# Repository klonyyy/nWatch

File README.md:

# nWatch
My wristwatch code repository

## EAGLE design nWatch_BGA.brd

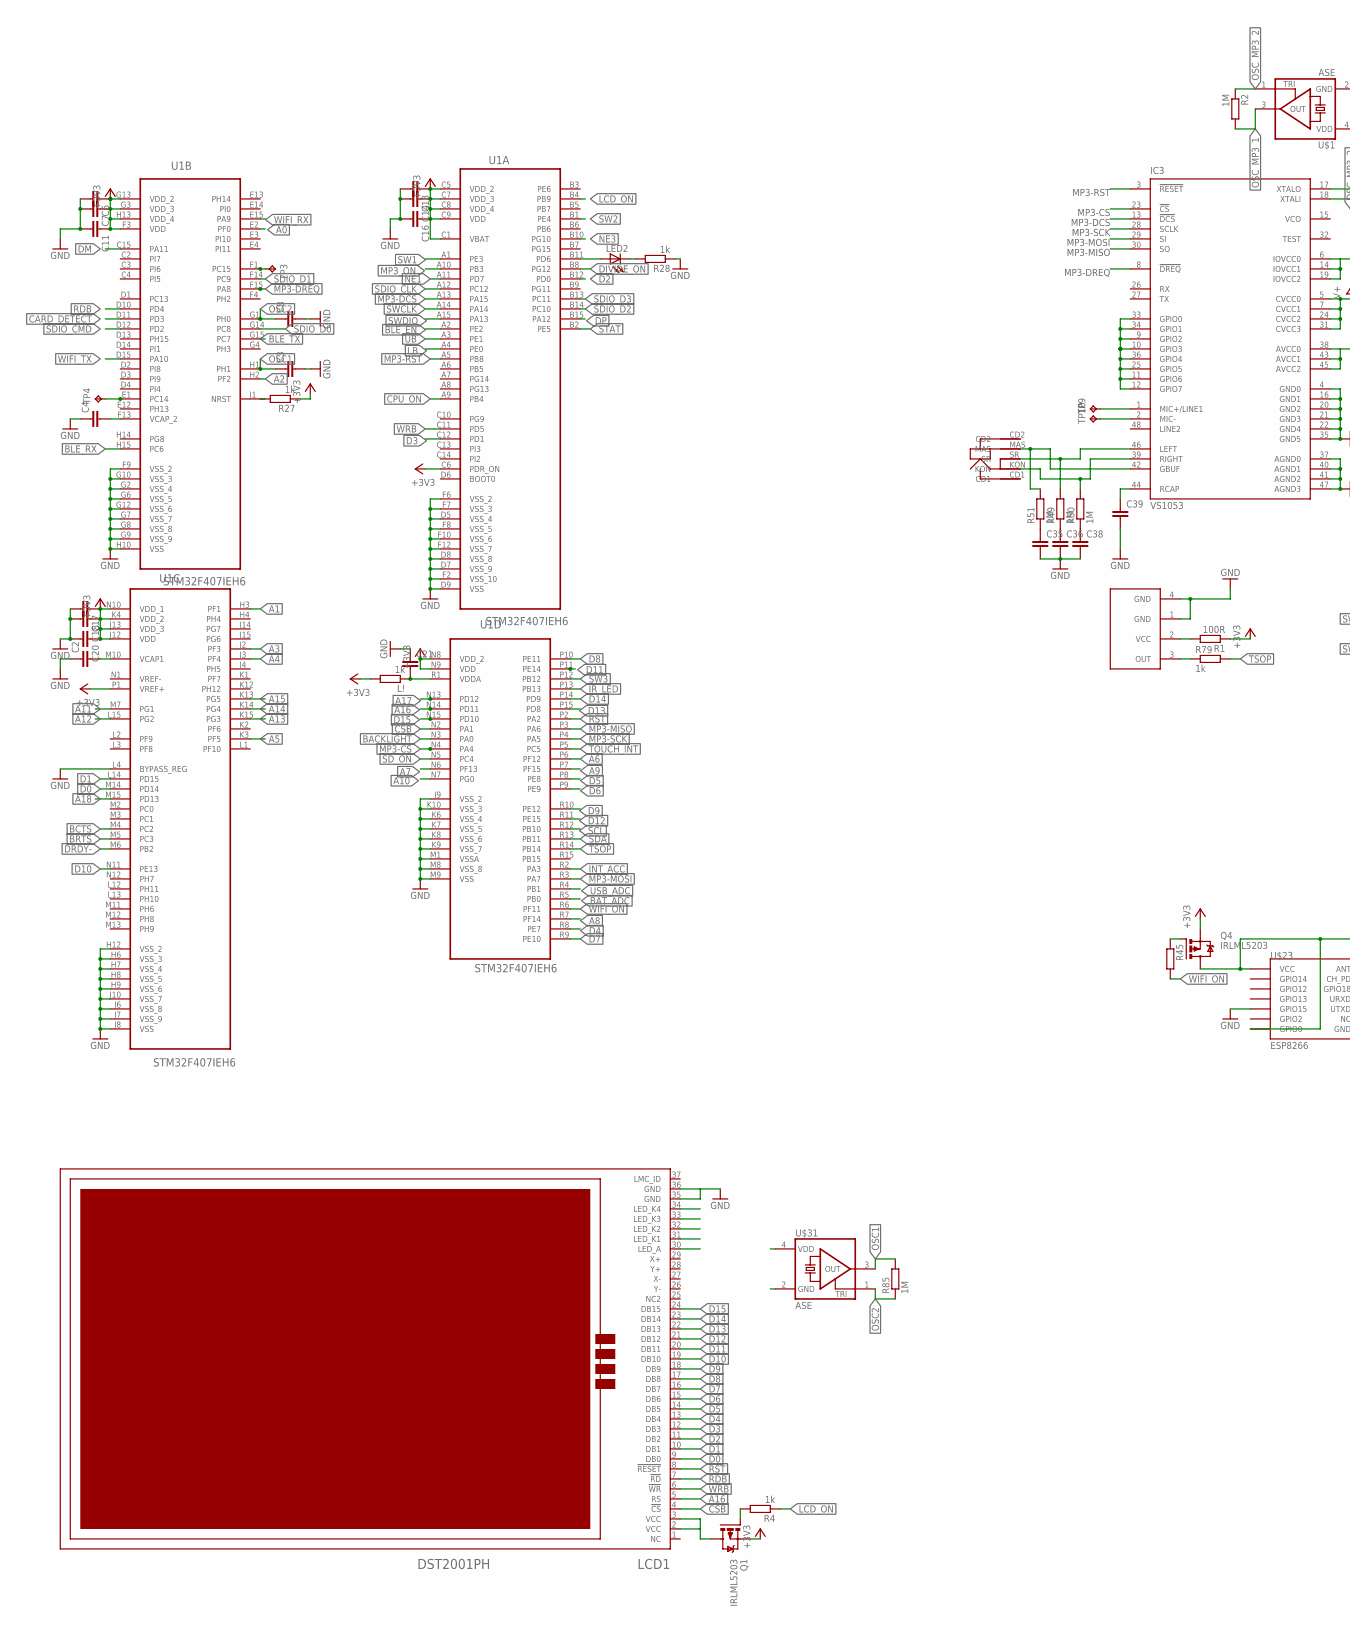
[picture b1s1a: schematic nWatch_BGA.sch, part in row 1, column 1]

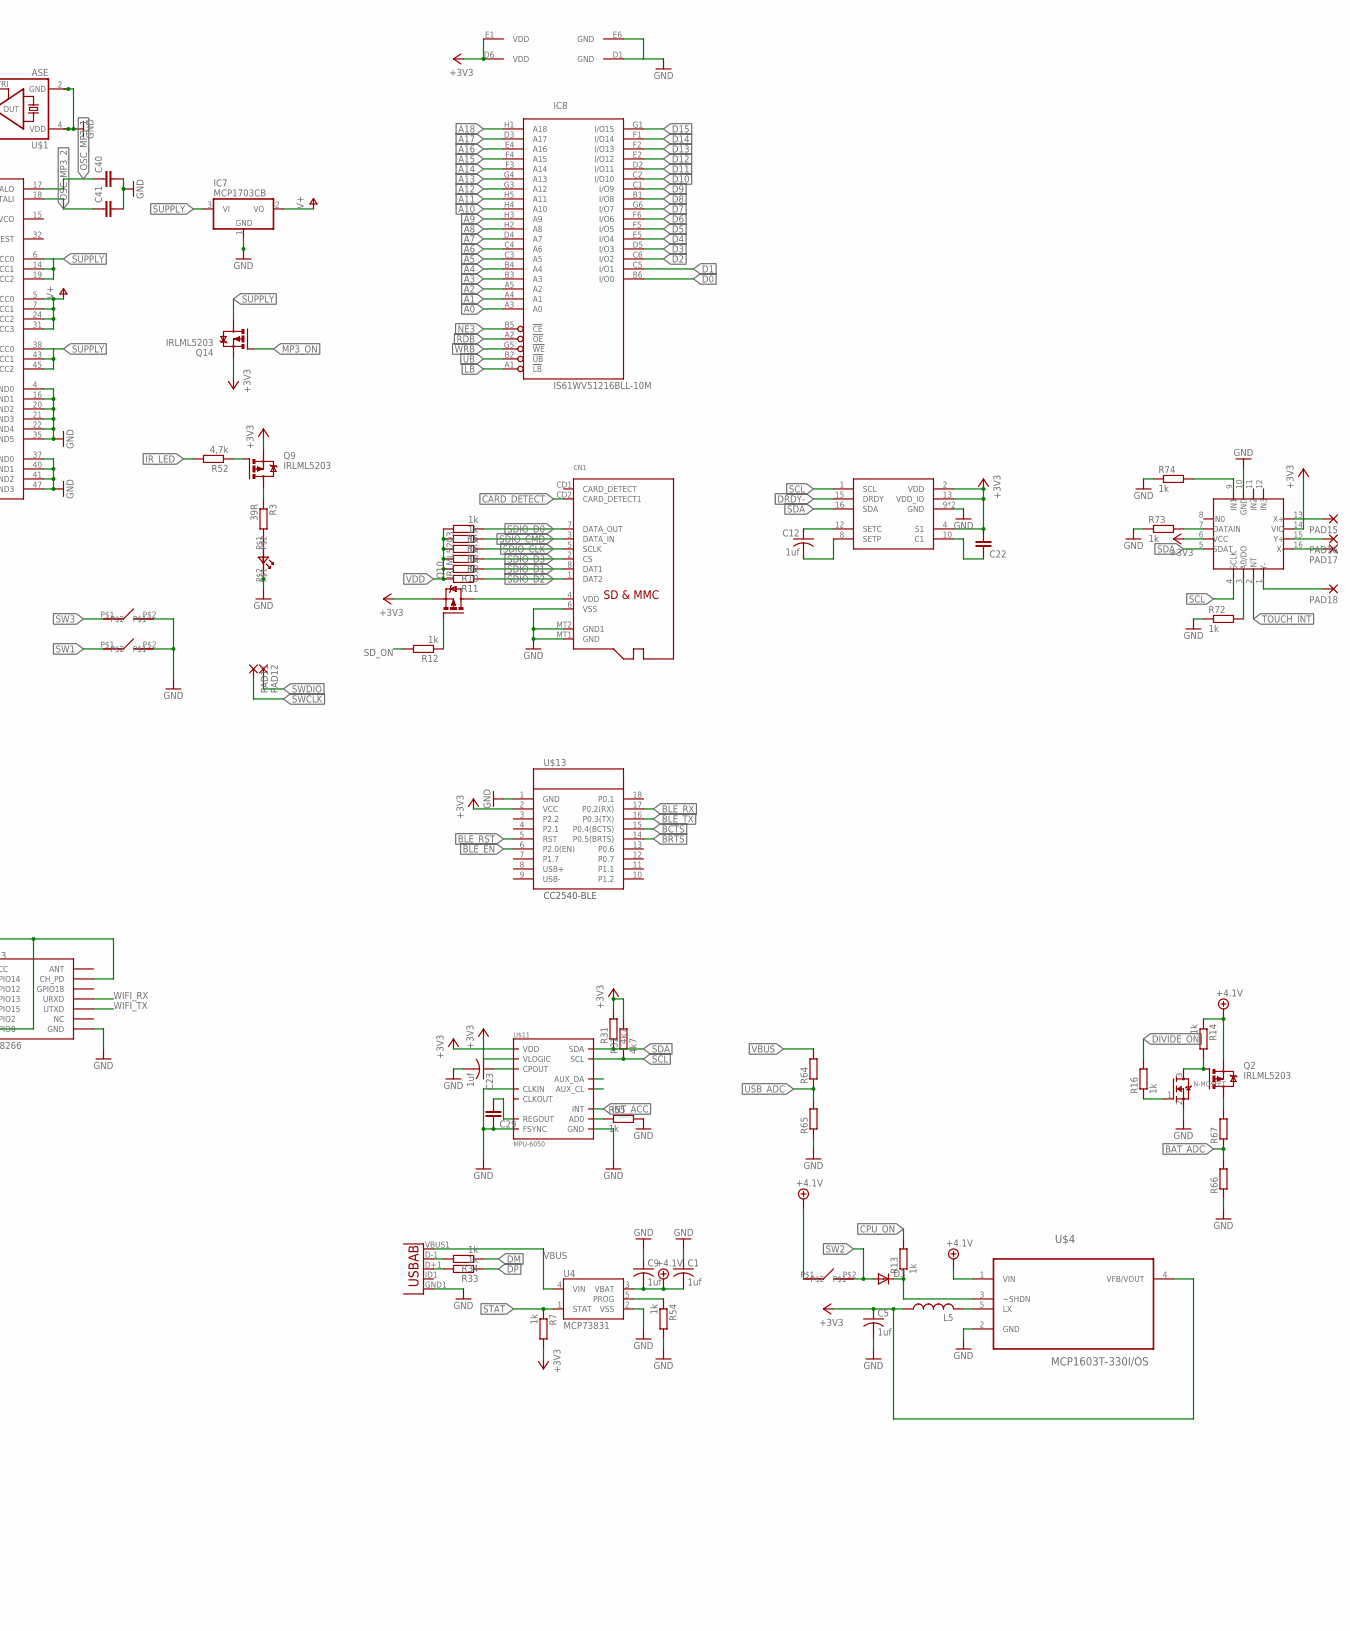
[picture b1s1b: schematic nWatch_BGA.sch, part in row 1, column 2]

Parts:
C1, C5, C9, C12, C23: 1uf; C0805K
C2, C3, C4, C6, C7, C8, C11, C13, C14, C16, C17, C18, C20, C21, C35, C36, C38, C39, C40, C41: C-EUC0402; C0402
C22, C29: C-EUC0603K; C0603K
CN1: MICROSD
D3: MBR0520LT; SOD123
IC3: VS1053; LQFP-48
IC7: MCP1703CB; SOT23
IC8: IS61WV51216BLL-10M; TFBGA48_9X11
L5: L-USL2825P; L2825P
L!: 1k; R0402
LCD1: DST2001PH
LED2: LEDCHIPLED_0603; CHIPLED_0603
N-MOSFET: MOSFET-NREFLOW; SOT23
PAD11, PAD12, PAD15, PAD16, PAD17, PAD18: SMD2; SMD1,27-2,54
Q1, Q2, Q4, Q9, Q10, Q14: IRLML5203; MICRO3
R1: 100R; R0402
R2, R49, R50, R51, R85: 1M; R0402
R3: 39R; R0402
R4, R5, R6, R7, R8, R9, R10, R11, R12, R13, R14, R16, R27, R28, R33, R34, R54, R55, R72, R73, R74, R79: 1k; R0402
R31, R32: 4k7; R0402
R45: R-EU_R0603; R0603
R52: 4,7k; R0402
R64, R65, R66, R67: R-EU_R0402; R0402
TP3, TP4, TP9, TP10: TPTP08SQ; TP08SQ
U1: STM32F407IEH6; BGA176C65P15X15_1000X1000X60
U4: MCP73831; SOT23-5
U5: USB""; USB-MICRO-SMD
U$1, U$31: ASE
U$2: TSOP77338TS; TSOP77338
U$4: MCP1603T-330I/OS; SOT95P280X110-5N
U$5, U$16, U$30: SWITCHSMD
U$11: MPU-6050; QFN.24.4X4
U$12: HMC5883L; LPCC16
U$13: MOJ_BLEMOJ_BLE; CC2540-MINI-BLE
U$15: STMPE811; QFN-16
U$23: ESP8266; ESP-03
U$26: VISHAY_IRLED
U$32: MOJ_JACK

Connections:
+3V3: C5.1, C6.1, C7.1, C11.1, C13.1, C14.1, C16.1, C17.1, C18.1, C20.1, C22.2, IC8.D6 (VDD), IC8.E1 (VDD), L5.1, L!.2, Q1.2 (S), Q4.2 (S), Q9.2 (S), Q10.2 (S), Q14.2 (S), R1.1, R7.2, R27.1, R31.2, R32.2, U1.C1 (VBAT), U1.C5 (VDD_2), U1.C6 (PDR_ON), U1.C7 (VDD_3), U1.C8 (VDD_4), U1.C9 (VDD), U1.F3 (VDD), U1.G3 (VDD_3), U1.G13 (VDD_2), U1.H13 (VDD_4), U1.J12 (VDD), U1.J13 (VDD_3), U1.K4 (VDD_2), U1.N8 (VDD_2), U1.N9 (VDD), U1.N10 (VDD_1), U1.P1 (VREF+), U$4.4 (VFB/VOUT), U$11.8 (VLOGIC), U$11.13 (VDD), U$12.2 (VDD), U$12.4 (S1), U$12.13 (VDD_IO), U$13.2 (VCC), U$15.6 (VCC), U$15.14 (VIO)
+4.1V: C1.2, C9.2, Q2.2 (S), R14.1, U4.3 (VBAT), U$4.1 (VIN), U$5.P$1
A0: IC8.A3 (A0), U1.E2 (PF0)
A1: IC8.A4 (A1), U1.H3 (PF1)
A2: IC8.A5 (A2), U1.H2 (PF2)
A3: IC8.B3 (A3), U1.J2 (PF3)
A4: IC8.B4 (A4), U1.J3 (PF4)
A5: IC8.C3 (A5), U1.K3 (PF5)
A6: IC8.C4 (A6), U1.P6 (PF12)
A7: IC8.D4 (A7), U1.N6 (PF13)
A8: IC8.H2 (A8), U1.R7 (PF14)
A9: IC8.H3 (A9), U1.P7 (PF15)
A10: IC8.H4 (A10), U1.N7 (PG0)
A11: IC8.H5 (A11), U1.M7 (PG1)
A12: IC8.G3 (A12), U1.L15 (PG2)
A13: IC8.G4 (A13), U1.K15 (PG3)
A14: IC8.F3 (A14), U1.K14 (PG4)
A15: IC8.F4 (A15), U1.K13 (PG5)
A16: IC8.E4 (A16), LCD1.5 (RS), U1.N14 (PD11)
A17: IC8.D3 (A17), U1.N13 (PD12)
A18: IC8.H1 (A18), U1.M15 (PD13)
BACKLIGHT: U1.N3 (PA0)
BAT_ADC: R66.2, R67.1, U1.R5 (PB0)
BCTS: U1.M4 (PC2), U$13.15 (P0.4(BCTS))
BLE_EN: U1.A2 (PE2), U$13.6 (P2.0(EN))
BLE_RST: U$13.5 (RST)
BLE_RX: U1.H15 (PC6), U$13.17 (P0.2(RX))
BLE_TX: U1.G15 (PC7), U$13.16 (P0.3(TX))
BRTS: U1.M5 (PC3), U$13.14 (P0.5(BRTS))
CARD_DETECT: CN1.CD2 (CARD_DETECT1), U1.D11 (PD3)
CPU_ON: R13.2, U1.A9 (PB4)
CSB: LCD1.4 (!CS), U1.N2 (PA1)
D0: IC8.B6 (I/O0), LCD1.9 (DB0), U1.M14 (PD14)
D1: IC8.C5 (I/O1), LCD1.10 (DB1), U1.L14 (PD15)
D2: IC8.C6 (I/O2), LCD1.11 (DB2), U1.B12 (PD0)
D3: IC8.D5 (I/O3), LCD1.12 (DB3), U1.C12 (PD1)
D4: IC8.E5 (I/O4), LCD1.13 (DB4), U1.R8 (PE7)
D5: IC8.F5 (I/O5), LCD1.14 (DB5), U1.P8 (PE8)
D6: IC8.F6 (I/O6), LCD1.15 (DB6), U1.P9 (PE9)
D7: IC8.G6 (I/O7), LCD1.16 (DB7), U1.R9 (PE10)
D8: IC8.B1 (I/O8), LCD1.17 (DB8), U1.P10 (PE11)
D9: IC8.C1 (I/O9), LCD1.18 (DB9), U1.R10 (PE12)
D10: IC8.C2 (I/O10), LCD1.19 (DB10), U1.N11 (PE13)
D11: IC8.D2 (I/O11), LCD1.20 (DB11), U1.P11 (PE14)
D12: IC8.E2 (I/O12), LCD1.21 (DB12), U1.R11 (PE15)
D13: IC8.F2 (I/O13), LCD1.22 (DB13), U1.P15 (PD8)
D14: IC8.F1 (I/O14), LCD1.23 (DB14), U1.P14 (PD9)
D15: IC8.G1 (I/O15), LCD1.24 (DB15), U1.N15 (PD10)
DIVIDE_ON: R16.2, U1.B8 (PG12)
DM: R34.1, U1.C15 (PA11)
DP: R33.1, U1.B15 (PA12)
DRDY-: U1.M6 (PB2), U$12.15 (DRDY)
GND: C1.1, C2.1, C3.2, C4.1, C5.2, C6.2, C7.2, C8.2, C9.1, C11.2, C13.2, C14.2, C16.2, C17.2, C18.2, C20.2, C21.1, C23.2, C29.1, C35.2, C36.2, C38.2, C39.2, C40.2, C41.2, CN1.6 (VSS), CN1.MT1 (GND), CN1.MT2 (GND1), IC3.4 (GND0), IC3.16 (GND1), IC3.20 (GND2), IC3.21 (GND3), IC3.22 (GND4), IC3.35 (GND5), IC3.37 (AGND0), IC3.40 (AGND1), IC3.41 (AGND2), IC3.47 (AGND3), IC7.1 (GND), IC8.D1 (GND), IC8.E6 (GND), LCD1.35 (GND), LCD1.36 (GND), N-MOSFET.2 (S), R28.1, R54.2, R55.2, R65.1, R66.1, R72.1, R73.1, R74.1, U1.D5 (VSS_4), U1.D7 (VSS_9), U1.D8 (VSS_8), U1.D9 (VSS), U1.F2 (VSS_10), U1.F6 (VSS_2), U1.F7 (VSS_3), U1.F8 (VSS_5), U1.F9 (VSS_2), U1.F10 (VSS_6), U1.F12 (VSS_7), U1.G2 (VSS_4), U1.G6 (VSS_5), U1.G7 (VSS_7), U1.G8 (VSS_8), U1.G9 (VSS_9), U1.G10 (VSS_3), U1.G12 (VSS_6), U1.H6 (VSS_3), U1.H7 (VSS_4), U1.H8 (VSS_5), U1.H9 (VSS_6), U1.H10 (VSS), U1.H12 (VSS_2), U1.J6 (VSS_8), U1.J7 (VSS_9), U1.J8 (VSS), U1.J9 (VSS_2), U1.J10 (VSS_7), U1.K6 (VSS_4), U1.K7 (VSS_5), U1.K8 (VSS_6), U1.K9 (VSS_7), U1.K10 (VSS_3), U1.L4 (BYPASS_REG), U1.M1 (VSSA), U1.M8 (VSS_8), U1.M9 (VSS), U4.2 (VSS), U5.GND1 (GND), U$1.2 (GND), U$1.4 (VDD), U$2.1 (GND), U$2.4 (GND), U$4.2 (GND), U$11.1 (CLKIN), U$11.11 (FSYNC), U$11.18 (GND), U$12.9 (GND), U$12.11 (GND), U$13.1 (GND), U$15.10 (GND), U$16.P$2, U$23.GND, U$23.GPIO15, U$26.P$2, U$30.P$2, U$31.2 (GND), U$31.4 (VDD)
INT_ACC: U1.R2 (PA3), U$11.12 (INT)
IR_LED: R52.2, U1.P13 (PB13)
LB: IC8.A1 (!LB), U1.A4 (PE0)
LCD_ON: R4.1, U1.B4 (PB9)
MP3-CS: IC3.23 (!CS), U1.N4 (PA4)
MP3-DCS: IC3.13 (!DCS), U1.A13 (PA15)
MP3-DREQ: IC3.8 (!DREQ), U1.F15 (PA8)
MP3-MISO: IC3.30 (SO), U1.P3 (PA6)
MP3-MOSI: IC3.29 (SI), U1.R3 (PA7)
MP3-RST: IC3.3 (!RESET), U1.A5 (PB8)
MP3-SCK: IC3.28 (SCLK), U1.P4 (PA5)
MP3_ON: Q14.1 (G), U1.A10 (PB3)
unnamed: LCD1.2 (VCC), LCD1.3 (VCC), Q1.3 (D)
unnamed: Q1.1 (G), R4.2
unnamed: R79.1, U$2.3 (OUT)
unnamed: R3.2, U$26.P$1
unnamed: C21.2, L!.1, U1.R1 (VDDA)
unnamed: N-MOSFET.3 (D), Q2.1 (G), R14.2
unnamed: C2.2, U1.M10 (VCAP1)
unnamed: C4.2, U1.F13 (VCAP_2)
unnamed: D3.C, R13.1, U$4.3 (~SHDN)
unnamed: N-MOSFET.1 (G), R16.1
unnamed: L5.2, U$4.5 (LX)
unnamed: Q2.3 (D), R67.2
unnamed: TP4.TP, U1.E1 (PC14)
unnamed: TP3.TP, U1.F1 (PC15)
unnamed: R27.2, U1.J1 (NRST)
unnamed: LED2.A, U1.B11 (PD6)
unnamed: LED2.C, R28.2
unnamed: C23.1, U$11.20 (CPOUT)
unnamed: R55.1, U$11.9 (AD0)
unnamed: R54.1, U4.5 (PROG)
unnamed: R33.2, U5.D+1 (D+)
unnamed: R34.2, U5.D-1 (D-)
unnamed: C12.1, U$12.12 (SETC)
unnamed: C12.2, U$12.8 (SETP)
unnamed: C22.1, U$12.10 (C1)
unnamed: C29.2, U$11.10 (REGOUT)
unnamed: R73.2, U$15.7 (DATAIN)
unnamed: R74.2, U$15.9 (IN1)
unnamed: R72.2, U$15.3 (A0/DO)
unnamed: Q10.1 (G), R12.1
unnamed: IC3.42 (GBUF), R51.2, U$32.MAS
unnamed: IC3.46 (LEFT), R49.2, U$32.SR
unnamed: IC3.39 (RIGHT), R50.2, U$32.KON
unnamed: C39.1, IC3.44 (RCAP)
unnamed: IC3.9 (GPIO2), IC3.10 (GPIO3), IC3.11 (GPIO6), IC3.12 (GPIO7), IC3.25 (GPIO5), IC3.33 (GPIO0), IC3.34 (GPIO1), IC3.36 (GPIO4)
unnamed: Q9.1 (G), R52.1
unnamed: Q9.3 (D), R3.1
unnamed: Q4.3 (D), U$23.CH_PD, U$23.GPIO0, U$23.VCC
unnamed: Q4.1 (G), R45.1
unnamed: C35.1, R51.1
unnamed: C36.1, R49.1
unnamed: C38.1, R50.1
unnamed: PAD18.1, U$15.1 (Y-)
unnamed: PAD17.1, U$15.16 (X-)
unnamed: PAD15.1, U$15.13 (X+)
unnamed: PAD16.1, U$15.15 (Y+)
unnamed: R1.2, U$2.2 (VCC)
unnamed: IC3.2 (MIC-), TP10.TP
unnamed: IC3.1 (MIC+/LINE1), TP9.TP
NE1: U1.A11 (PD7)
NE3: IC8.B5 (!CE), U1.B10 (PG10)
OSC1: C3.1, R85.2, U1.H1, U$31.3 (OUT)
OSC2: C8.1, R85.1, U1.G1 (PH0), U$31.1 (TRI)
OSC_MP3_1: C40.1, IC3.17 (XTALO), R2.2, U$1.3 (OUT)
OSC_MP3_2: C41.1, IC3.18 (XTALI), R2.1, U$1.1 (TRI)
P2.2: U$13.3 (P2.2)
RDB: IC8.A2 (!OE), LCD1.7 (!RD), U1.D10 (PD4)
RST: LCD1.8 (!RESET), U1.P2 (PA2)
SCL: R32.1, U1.R12 (PB10), U$11.23 (SCL), U$12.1 (SCL), U$15.4 (SCLK)
SDA: R31.1, U1.R13 (PB11), U$11.24 (SDA), U$12.16 (SDA), U$15.5 (SDAT)
SDIO_CLK: CN1.5 (SCLK), R8.1, U1.A12 (PC12)
SDIO_CMD: CN1.3 (DATA_IN), R6.1, U1.D12 (PD2)
SDIO_D0: CN1.7 (DATA_OUT), R5.1, U1.G14 (PC8)
SDIO_D1: CN1.8 (DAT1), R10.1, U1.F14 (PC9)
SDIO_D2: CN1.1 (DAT2), R11.1, U1.B14 (PC10)
SDIO_D3: CN1.2 (CS), R9.1, U1.B13 (PC11)
SD_ON: R12.2, U1.N5 (PC4)
STAT: R7.1, U1.B2 (PE5), U4.1 (STAT)
SUPPLY: IC3.6 (IOVCC0), IC3.14 (IOVCC1), IC3.19 (IOVCC2), IC3.38 (AVCC0), IC3.43 (AVCC1), IC3.45 (AVCC2), IC7.3 (VI), Q14.3 (D)
SW1: U1.A1 (PE3), U$16.P$1
SW2: D3.A, U1.B1 (PE4), U$5.P$2
SW3: U1.P12 (PB12), U$30.P$1
SWCLK: PAD11.1, U1.A14
SWDIO: PAD12.1, U1.A15 (PA13)
TOUCH_INT: U1.P5 (PC5), U$15.2 (INT)
TSOP: R79.2, U1.R14 (PB14)
UB: IC8.B2 (!UB), U1.A3 (PE1)
USB_ADC: R64.1, R65.2, U1.R4 (PB1)
V+: IC3.5 (CVCC0), IC3.7 (CVCC1), IC3.24 (CVCC2), IC3.31 (CVCC3), IC7.2 (VO)
VBUS: R64.2, U4.4 (VIN), U5.VBUS1 (VBUS)
VDD: CN1.4 (VDD), Q10.3 (D), R5.2, R6.2, R8.2, R9.2, R10.2, R11.2
VREF-: U1.N1 (VREF-)
WIFI_ON: R45.2, U1.R6 (PF11)
WIFI_RX: U1.E15 (PA9), U$23.URXD
WIFI_TX: U1.D15 (PA10), U$23.UTXD
WRB: IC8.G5 (!WE), LCD1.6 (!WR), U1.C11 (PD5)

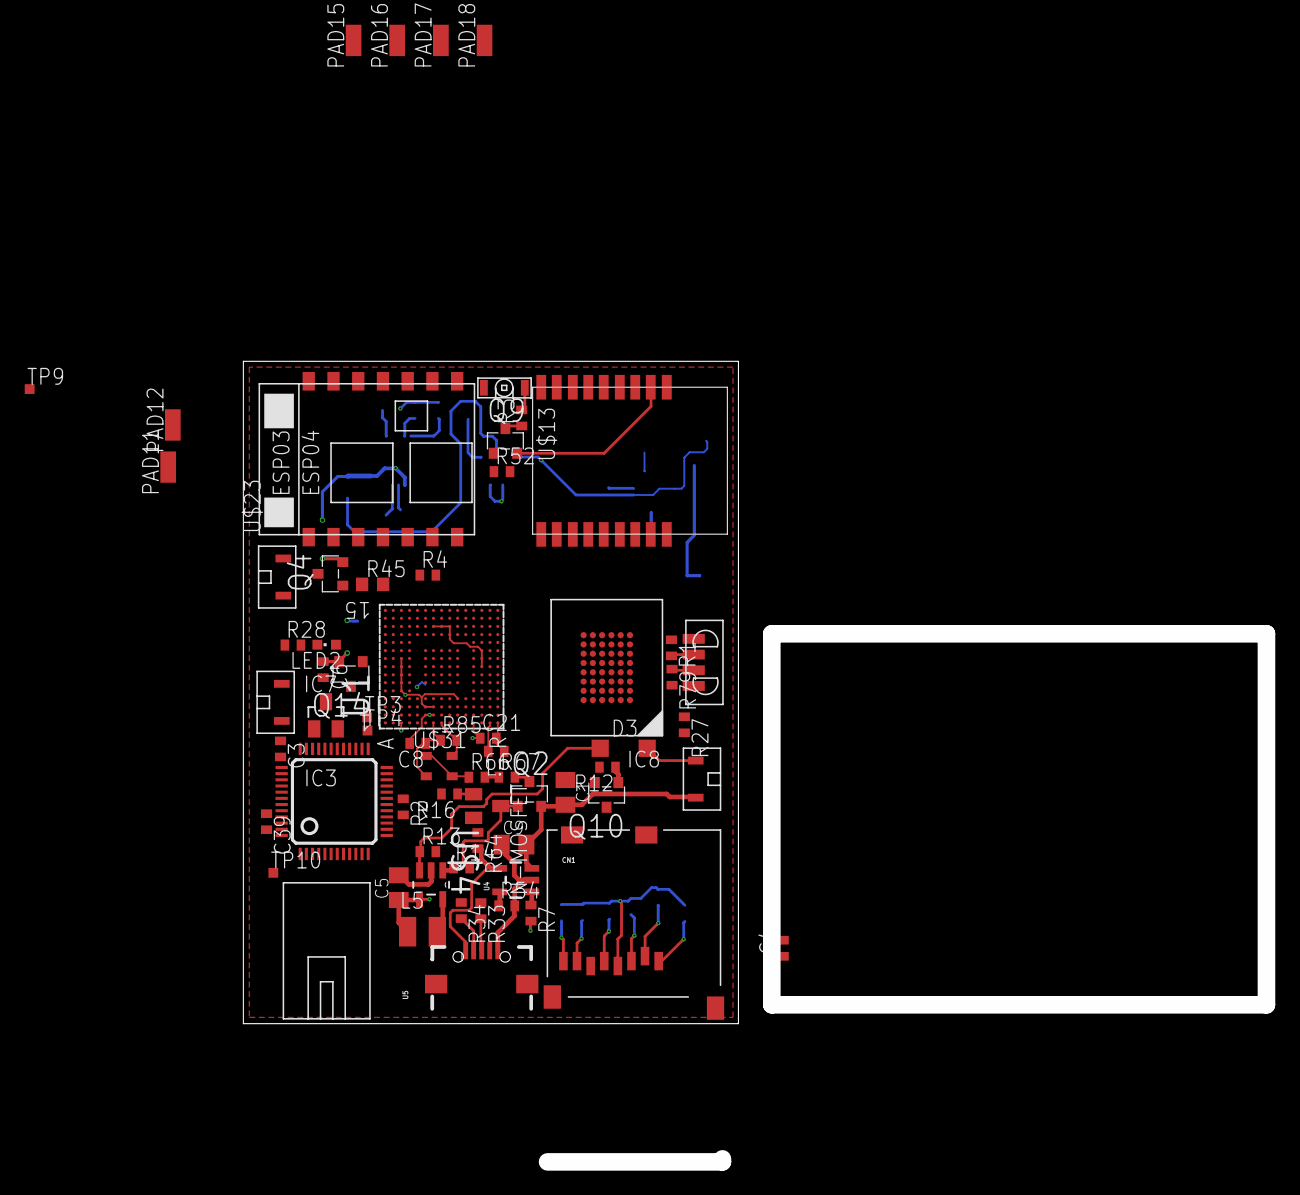
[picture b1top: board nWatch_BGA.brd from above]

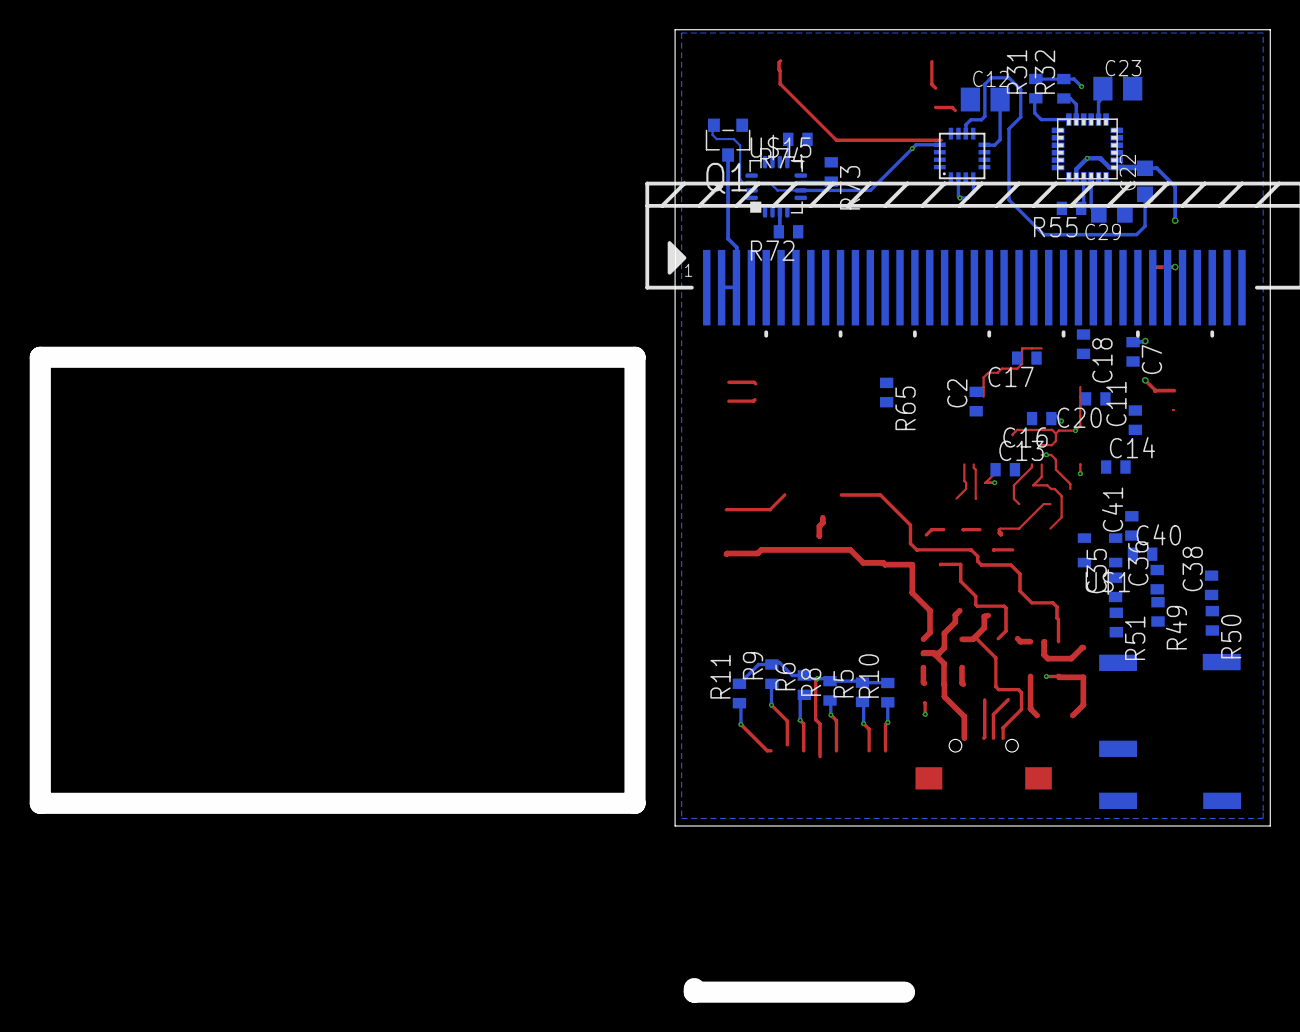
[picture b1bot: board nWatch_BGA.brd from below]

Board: 4 copper layers, 82.7 x 64.7 mm, 107 parts (41 on the bottom side), 146 nets.

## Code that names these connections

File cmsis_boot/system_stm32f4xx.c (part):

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// +-------------------+--------------------+------------------+------------------+
// +                       SRAM pins assignment                                   +
// +-------------------+--------------------+------------------+------------------+
// | PD0  <-> FSMC_D2  | PE0  <-> FSMC_NBL0 | PF0  <-> FSMC_A0 | PG0 <-> FSMC_A10 |
// | PD1  <-> FSMC_D3  | PE1  <-> FSMC_NBL1 | PF1  <-> FSMC_A1 | PG1 <-> FSMC_A11 |
// | PD4  <-> FSMC_NOE | PE3  <-> FSMC_A19  | PF2  <-> FSMC_A2 | PG2 <-> FSMC_A12 |
// | PD5  <-> FSMC_NWE | PE4  <-> FSMC_A20  | PF3  <-> FSMC_A3 | PG3 <-> FSMC_A13 |
// | PD8  <-> FSMC_D13 | PE7  <-> FSMC_D4   | PF4  <-> FSMC_A4 | PG4 <-> FSMC_A14 |
// | PD9  <-> FSMC_D14 | PE8  <-> FSMC_D5   | PF5  <-> FSMC_A5 | PG5 <-> FSMC_A15 |
// | PD10 <-> FSMC_D15 | PE9  <-> FSMC_D6   | PF12 <-> FSMC_A6 | PG9 <-> FSMC_NE2 |
// | PD11 <-> FSMC_A16 | PE10 <-> FSMC_D7   | PF13 <-> FSMC_A7 |------------------+
// | PD12 <-> FSMC_A17 | PE11 <-> FSMC_D8   | PF14 <-> FSMC_A8 |
// | PD13 <-> FSMC_A18 | PE12 <-> FSMC_D9   | PF15 <-> FSMC_A9 |
// | PD14 <-> FSMC_D0  | PE13 <-> FSMC_D10  |------------------+
// | PD15 <-> FSMC_D1  | PE14 <-> FSMC_D11  |
// |                   | PE15 <-> FSMC_D12  |
// +-------------------+--------------------+
//*/
//   /* Enable GPIOD, GPIOE, GPIOF and GPIOG interface clock */
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
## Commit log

2015-12-05 Update README.md
    OK
2015-12-05 repo
2015-12-30 test1
2015-12-31 test2
2016-01-01 test3
2016-01-03 test4
2016-01-04 test6
2016-01-04 test7
2016-01-08 update 1
2016-01-10 update2
2016-01-11 update3
2016-01-17 update eagle

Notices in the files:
cmsis_boot/system_stm32f4xx.c:
© COPYRIGHT 2011 STMicroelectronics
(C) COPYRIGHT 2011 STMicroelectronics *****END OF FILE
